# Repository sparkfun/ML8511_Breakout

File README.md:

ML8511 UV Sensor Breakout
=========================

[*ML8511 UV Sensor (SEN-12705)*](https://www.sparkfun.com/products/12705)

The ML8511 sensor detects ultraviolet light in the 280 to 390nm range.

Repository Contents
-------------------

* **/Firmware** - Example firmware for running the sensor
* **/Hardware** - All Eagle design files (.brd, .sch)
* **/Production** - Test bed files and production panel files
 
License Information
-------------------
The hardware is released under [Creative Commons ShareAlike 4.0 International](https://creativecommons.org/licenses/by-sa/4.0/).
The code is beerware; if you see me (or any other SparkFun employee) at the local, and you've found our code helpful, please buy us a round!

Distributed as-is; no warranty is given.

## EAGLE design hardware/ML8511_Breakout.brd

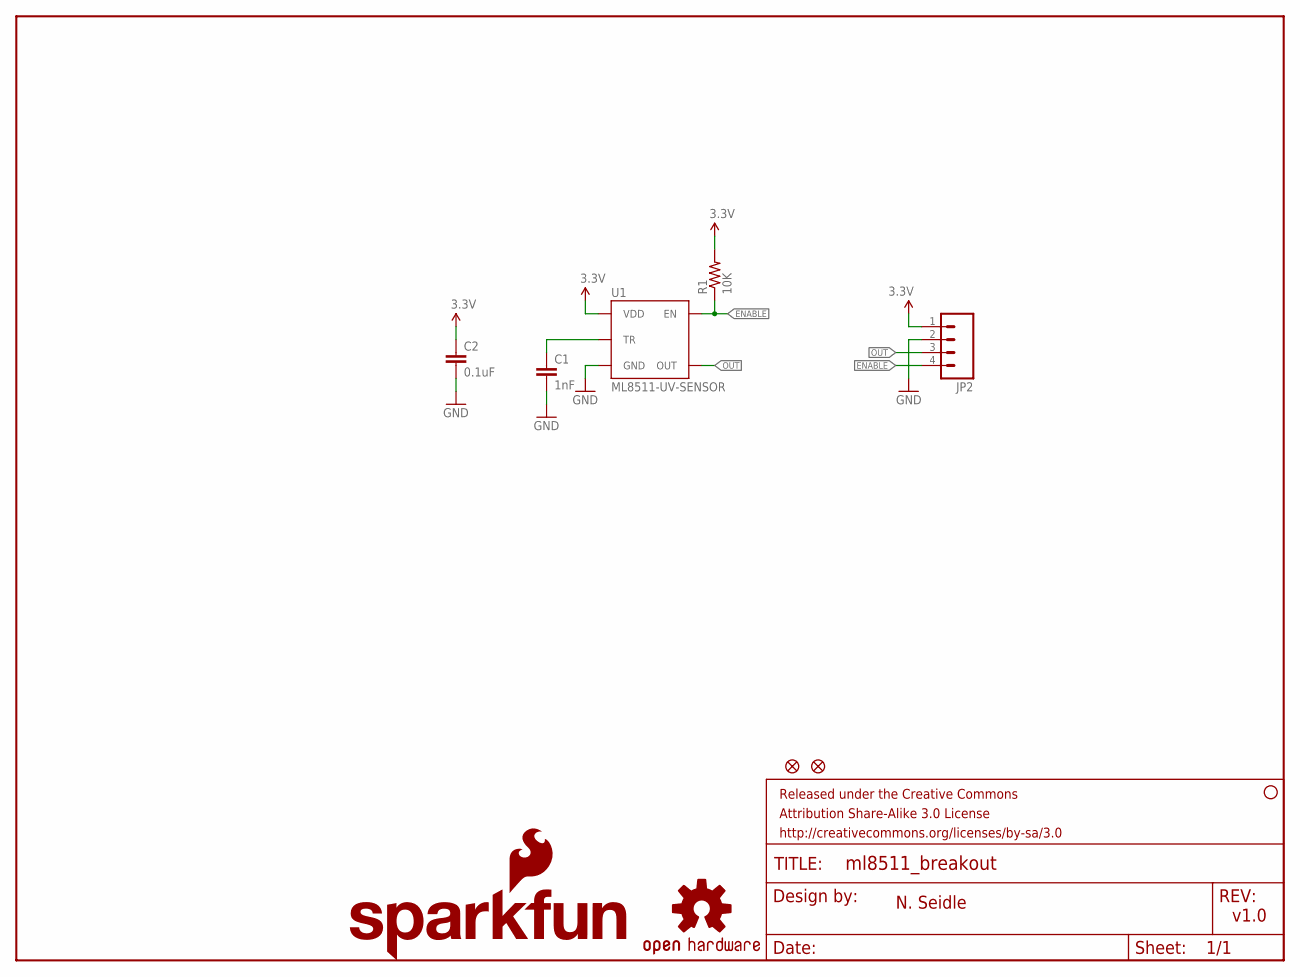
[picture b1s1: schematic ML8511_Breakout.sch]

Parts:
C1: 1nF; 0603-CAP
C2: 0.1uF; 0603-CAP
FID1, FID2: FIDUCIAL1X2; FIDUCIAL-1X2
FRAME2: FRAME-LETTER; CREATIVE_COMMONS
JP2: M04PTH; 1X04
LOGO2: OSHW-LOGOS; OSHW-LOGO-S
LOGO3: SFE_LOGO_FLAME.1_INCH; SFE_LOGO_FLAME_.1
LOGO4: SFE_LOGO_NAME.1_INCH; SFE_LOGO_NAME_.1
R1: 10K; 0603-RES
STANDOFF1: STAND-OFF
U1: ML8511-UV-SENSOR; ML8511

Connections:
3.3V: C2.1, JP2.1, R1.2, U1.7 (VDD)
ENABLE: JP2.4, R1.1, U1.4 (EN)
GND: C1.2, C2.2, JP2.2, U1.5 (GND)
unnamed: C1.1, U1.10 (TR)
OUT: JP2.3, U1.8 (OUT)

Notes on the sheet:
N. Seidle
v1.0

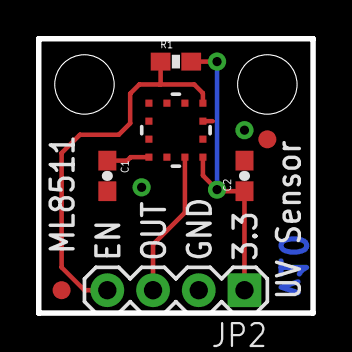
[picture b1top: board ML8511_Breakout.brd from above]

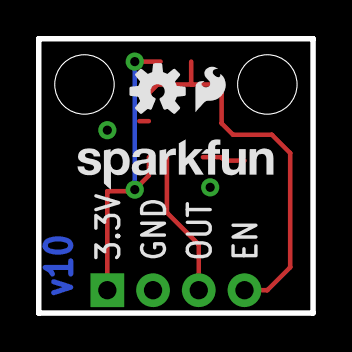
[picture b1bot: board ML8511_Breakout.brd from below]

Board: 2 copper layers, 15.2 x 15.2 mm, 13 parts (3 on the bottom side), 5 nets.

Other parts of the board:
STANDOFF2: STAND-OFF

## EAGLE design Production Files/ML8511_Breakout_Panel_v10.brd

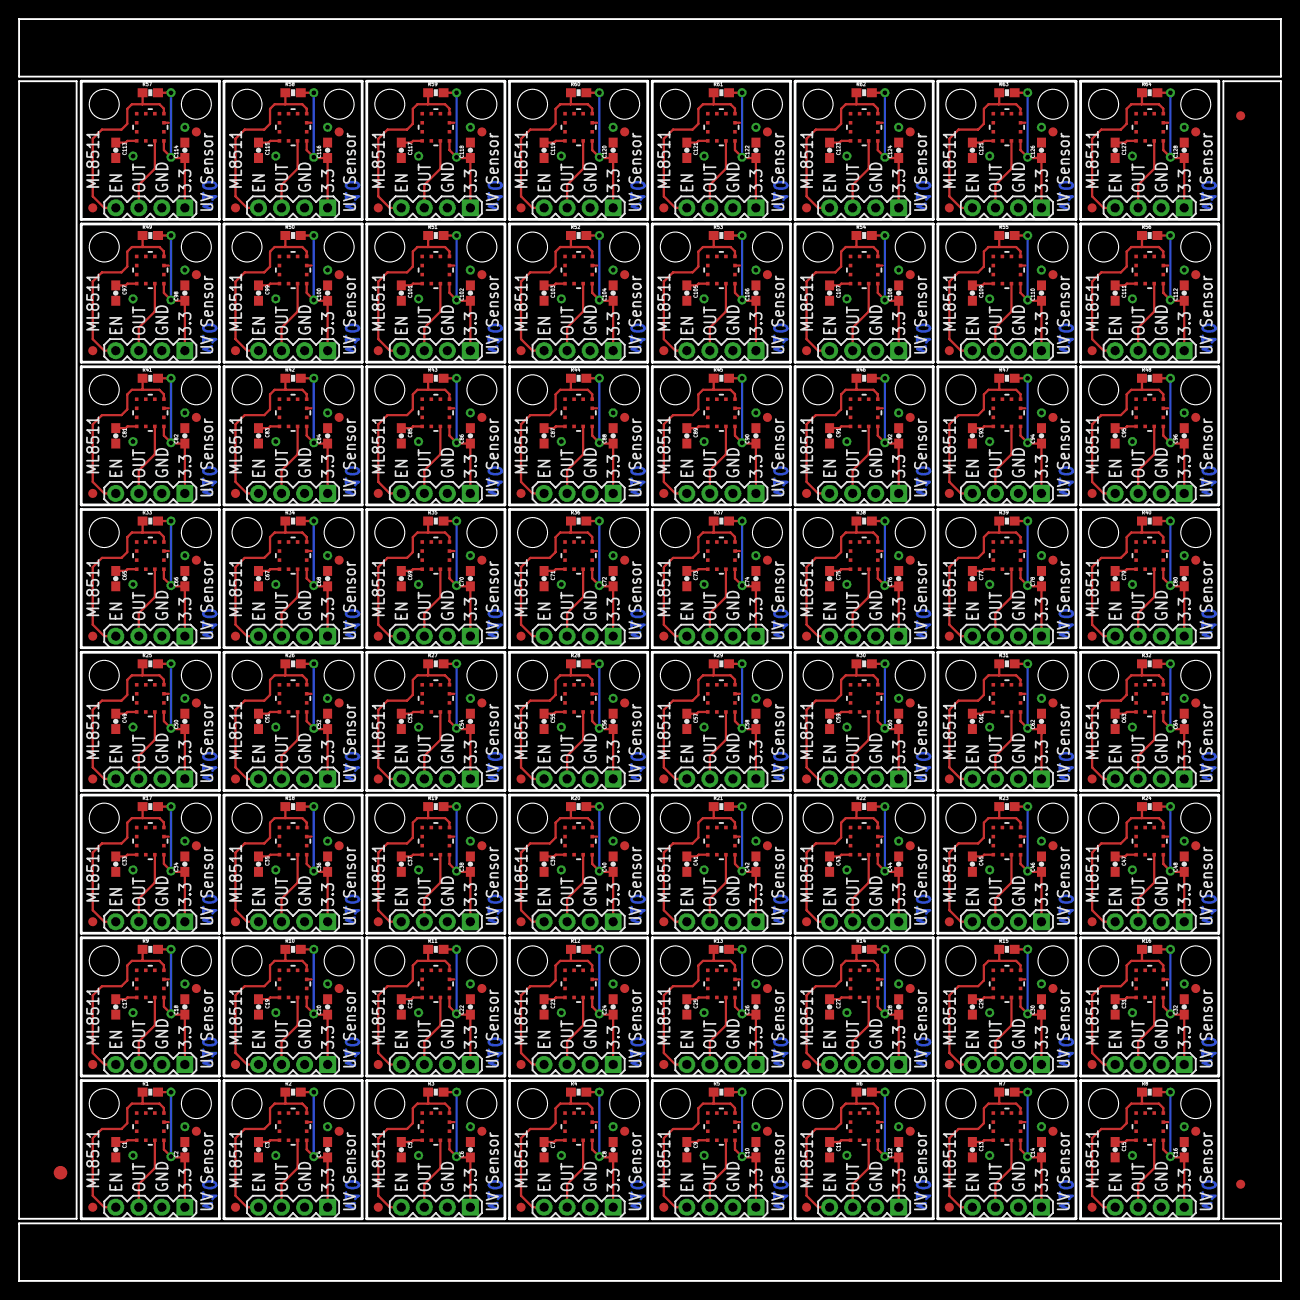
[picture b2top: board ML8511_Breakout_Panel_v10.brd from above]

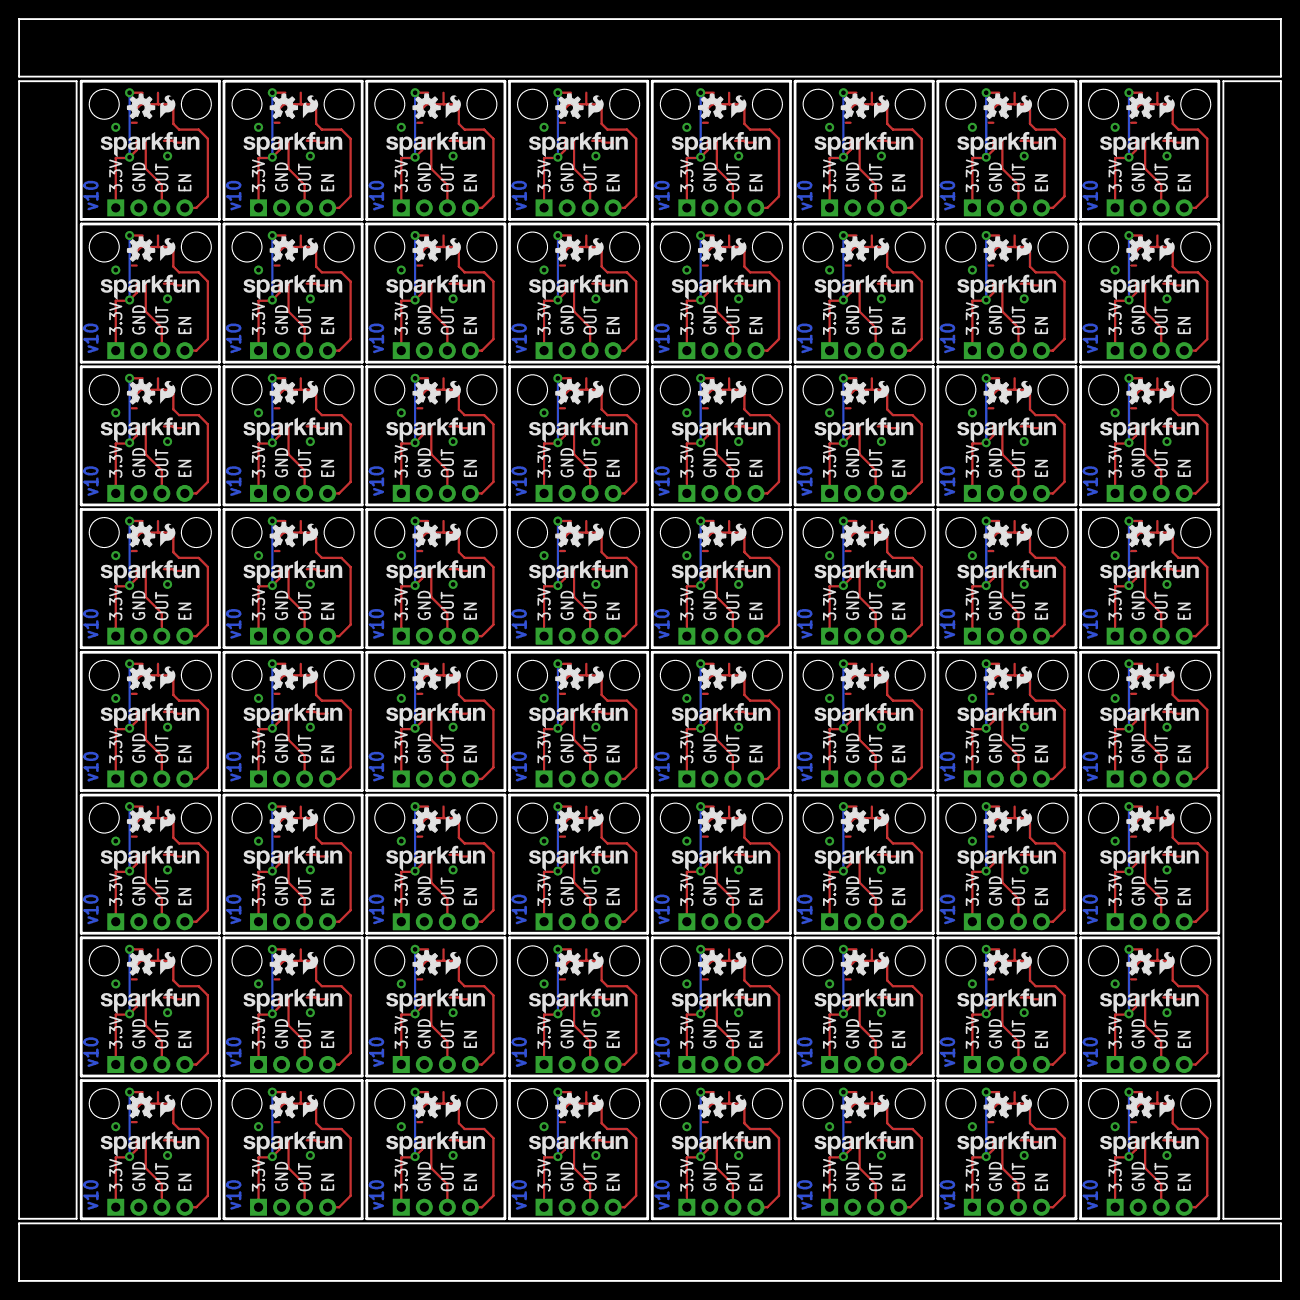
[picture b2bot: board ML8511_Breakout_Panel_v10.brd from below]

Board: 2 copper layers, 139.2 x 139.2 mm, 771 parts (192 on the bottom side), 320 nets.

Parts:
C1, C3, C5, C7, C9, C11, C13, C15, C17, C19, C21, C23, C25, C27, C29, C31, C33, C35, C37, C39, C41, C43, C45, C47, C49, C51, C53, C55, C57, C59, C61, C63, C65, C67, C69, C71, C73, C75, C77, C79, C81, C83, C85, C87, C89, C91, C93, C95, C97, C99, C101, C103, C105, C107, C109, C111, C113, C115, C117, C119, C121, C123, C125, C127: 1nF; 0603-CAP
C2, C4, C6, C8, C10, C12, C14, C16, C18, C20, C22, C24, C26, C28, C30, C32, C34, C36, C38, C40, C42, C44, C46, C48, C50, C52, C54, C56, C58, C60, C62, C64, C66, C68, C70, C72, C74, C76, C78, C80, C82, C84, C86, C88, C90, C92, C94, C96, C98, C100, C102, C104, C106, C108, C110, C112, C114, C116, C118, C120, C122, C124, C126, C128: 0.1uF; 0603-CAP
E$1: FIDUCIAL-1.5X3
E$4, E$5: FIDUCIAL-1X2
FID1, FID2, FID3, FID4, FID5, FID6, FID7, FID8, FID9, FID10, FID11, FID12, FID13, FID14, FID15, FID16, FID17, FID18, FID19, FID20, FID21, FID22, FID23, FID24, FID25, FID26, FID27, FID28, FID29, FID30, FID31, FID32, FID33, FID34, FID35, FID36, FID37, FID38, FID39, FID40, FID41, FID42, FID43, FID44, FID45, FID46, FID47, FID48, FID49, FID50, FID51, FID52, FID53, FID54, FID55, FID56, FID57, FID58, FID59, FID60, FID61, FID62, FID63, FID64, FID65, FID66, FID67, FID68, FID69, FID70, FID71, FID72, FID73, FID74, FID75, FID76, FID77, FID78, FID79, FID80, FID81, FID82, FID83, FID84, FID85, FID86, FID87, FID88, FID89, FID90, FID91, FID92, FID93, FID94, FID95, FID96, FID97, FID98, FID99, FID100, FID101, FID102, FID103, FID104, FID105, FID106, FID107, FID108, FID109, FID110, FID111, FID112, FID113, FID114, FID115, FID116, FID117, FID118, FID119, FID120, FID121, FID122, FID123, FID124, FID125, FID126, FID127, FID128: FIDUCIAL1X2; FIDUCIAL-1X2
JP1, JP2, JP3, JP4, JP5, JP6, JP7, JP8, JP9, JP10, JP11, JP12, JP13, JP14, JP15, JP16, JP17, JP18, JP19, JP20, JP21, JP22, JP23, JP24, JP25, JP26, JP27, JP28, JP29, JP30, JP31, JP32, JP33, JP34, JP35, JP36, JP37, JP38, JP39, JP40, JP41, JP42, JP43, JP44, JP45, JP46, JP47, JP48, JP49, JP50, JP51, JP52, JP53, JP54, JP55, JP56, JP57, JP58, JP59, JP60, JP61, JP62, JP63, JP64: 1X04
LOGO1, LOGO2, LOGO7, LOGO10, LOGO13, LOGO16, LOGO19, LOGO22, LOGO25, LOGO28, LOGO31, LOGO34, LOGO37, LOGO40, LOGO43, LOGO46, LOGO49, LOGO52, LOGO55, LOGO58, LOGO61, LOGO64, LOGO67, LOGO70, LOGO73, LOGO76, LOGO79, LOGO82, LOGO85, LOGO88, LOGO91, LOGO94, LOGO97, LOGO100, LOGO103, LOGO106, LOGO109, LOGO112, LOGO115, LOGO118, LOGO121, LOGO124, LOGO127, LOGO130, LOGO133, LOGO136, LOGO139, LOGO142, LOGO145, LOGO148, LOGO151, LOGO154, LOGO157, LOGO160, LOGO163, LOGO166, LOGO169, LOGO172, LOGO175, LOGO178, LOGO181, LOGO184, LOGO187, LOGO190: OSHW-LOGOS; OSHW-LOGO-S
LOGO3, LOGO5, LOGO8, LOGO11, LOGO14, LOGO17, LOGO20, LOGO23, LOGO26, LOGO29, LOGO32, LOGO35, LOGO38, LOGO41, LOGO44, LOGO47, LOGO50, LOGO53, LOGO56, LOGO59, LOGO62, LOGO65, LOGO68, LOGO71, LOGO74, LOGO77, LOGO80, LOGO83, LOGO86, LOGO89, LOGO92, LOGO95, LOGO98, LOGO101, LOGO104, LOGO107, LOGO110, LOGO113, LOGO116, LOGO119, LOGO122, LOGO125, LOGO128, LOGO131, LOGO134, LOGO137, LOGO140, LOGO143, LOGO146, LOGO149, LOGO152, LOGO155, LOGO158, LOGO161, LOGO164, LOGO167, LOGO170, LOGO173, LOGO176, LOGO179, LOGO182, LOGO185, LOGO188, LOGO191: SFE_LOGO_FLAME.1_INCH; SFE_LOGO_FLAME_.1
LOGO4, LOGO6, LOGO9, LOGO12, LOGO15, LOGO18, LOGO21, LOGO24, LOGO27, LOGO30, LOGO33, LOGO36, LOGO39, LOGO42, LOGO45, LOGO48, LOGO51, LOGO54, LOGO57, LOGO60, LOGO63, LOGO66, LOGO69, LOGO72, LOGO75, LOGO78, LOGO81, LOGO84, LOGO87, LOGO90, LOGO93, LOGO96, LOGO99, LOGO102, LOGO105, LOGO108, LOGO111, LOGO114, LOGO117, LOGO120, LOGO123, LOGO126, LOGO129, LOGO132, LOGO135, LOGO138, LOGO141, LOGO144, LOGO147, LOGO150, LOGO153, LOGO156, LOGO159, LOGO162, LOGO165, LOGO168, LOGO171, LOGO174, LOGO177, LOGO180, LOGO183, LOGO186, LOGO189, LOGO192: SFE_LOGO_NAME.1_INCH; SFE_LOGO_NAME_.1
R1, R2, R3, R4, R5, R6, R7, R8, R9, R10, R11, R12, R13, R14, R15, R16, R17, R18, R19, R20, R21, R22, R23, R24, R25, R26, R27, R28, R29, R30, R31, R32, R33, R34, R35, R36, R37, R38, R39, R40, R41, R42, R43, R44, R45, R46, R47, R48, R49, R50, R51, R52, R53, R54, R55, R56, R57, R58, R59, R60, R61, R62, R63, R64: 10K; 0603-RES
STANDOFF1, STANDOFF2, STANDOFF3, STANDOFF4, STANDOFF5, STANDOFF6, STANDOFF7, STANDOFF8, STANDOFF9, STANDOFF10, STANDOFF11, STANDOFF12, STANDOFF13, STANDOFF14, STANDOFF15, STANDOFF16, STANDOFF17, STANDOFF18, STANDOFF19, STANDOFF20, STANDOFF21, STANDOFF22, STANDOFF23, STANDOFF24, STANDOFF25, STANDOFF26, STANDOFF27, STANDOFF28, STANDOFF29, STANDOFF30, STANDOFF31, STANDOFF32, STANDOFF33, STANDOFF34, STANDOFF35, STANDOFF36, STANDOFF37, STANDOFF38, STANDOFF39, STANDOFF40, STANDOFF41, STANDOFF42, STANDOFF43, STANDOFF44, STANDOFF45, STANDOFF46, STANDOFF47, STANDOFF48, STANDOFF49, STANDOFF50, STANDOFF51, STANDOFF52, STANDOFF53, STANDOFF54, STANDOFF55, STANDOFF56, STANDOFF57, STANDOFF58, STANDOFF59, STANDOFF60, STANDOFF61, STANDOFF62, STANDOFF63, STANDOFF64, STANDOFF65, STANDOFF66, STANDOFF67, STANDOFF68, STANDOFF69, STANDOFF70, STANDOFF71, STANDOFF72, STANDOFF73, STANDOFF74, STANDOFF75, STANDOFF76, STANDOFF77, STANDOFF78, STANDOFF79, STANDOFF80, STANDOFF81, STANDOFF82, STANDOFF83, STANDOFF84, STANDOFF85, STANDOFF86, STANDOFF87, STANDOFF88, STANDOFF89, STANDOFF90, STANDOFF91, STANDOFF92, STANDOFF93, STANDOFF94, STANDOFF95, STANDOFF96, STANDOFF97, STANDOFF98, STANDOFF99, STANDOFF100, STANDOFF101, STANDOFF102, STANDOFF103, STANDOFF104, STANDOFF105, STANDOFF106, STANDOFF107, STANDOFF108, STANDOFF109, STANDOFF110, STANDOFF111, STANDOFF112, STANDOFF113, STANDOFF114, STANDOFF115, STANDOFF116, STANDOFF117, STANDOFF118, STANDOFF119, STANDOFF120, STANDOFF121, STANDOFF122, STANDOFF123, STANDOFF124, STANDOFF125, STANDOFF126, STANDOFF127, STANDOFF128: STAND-OFF
U1, U2, U3, U4, U5, U6, U7, U8, U9, U10, U11, U12, U13, U14, U15, U16, U17, U18, U19, U20, U21, U22, U23, U24, U25, U26, U27, U28, U29, U30, U31, U32, U33, U34, U35, U36, U37, U38, U39, U40, U41, U42, U43, U44, U45, U46, U47, U48, U49, U50, U51, U52, U53, U54, U55, U56, U57, U58, U59, U60, U61, U62, U63, U64: ML8511-UV-SENSOR; ML8511

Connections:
3.3V: C2.1, JP2.1, R1.2, U1.7
3.3V1: C4.1, JP1.1, R2.2, U2.7
3.3V2: C6.1, JP3.1, R3.2, U3.7
3.3V3: C8.1, JP4.1, R4.2, U4.7
3.3V4: C10.1, JP5.1, R5.2, U5.7
3.3V5: C12.1, JP6.1, R6.2, U6.7
3.3V6: C14.1, JP7.1, R7.2, U7.7
3.3V7: C16.1, JP8.1, R8.2, U8.7
3.3V8: C18.1, JP9.1, R9.2, U9.7
3.3V9: C20.1, JP10.1, R10.2, U10.7
3.3V10: C22.1, JP11.1, R11.2, U11.7
3.3V11: C24.1, JP12.1, R12.2, U12.7
3.3V12: C26.1, JP13.1, R13.2, U13.7
3.3V13: C28.1, JP14.1, R14.2, U14.7
3.3V14: C30.1, JP15.1, R15.2, U15.7
3.3V15: C32.1, JP16.1, R16.2, U16.7
3.3V16: C34.1, JP17.1, R17.2, U17.7
3.3V17: C36.1, JP18.1, R18.2, U18.7
3.3V18: C38.1, JP19.1, R19.2, U19.7
3.3V19: C40.1, JP20.1, R20.2, U20.7
3.3V20: C42.1, JP21.1, R21.2, U21.7
3.3V21: C44.1, JP22.1, R22.2, U22.7
3.3V22: C46.1, JP23.1, R23.2, U23.7
3.3V23: C48.1, JP24.1, R24.2, U24.7
3.3V24: C50.1, JP25.1, R25.2, U25.7
3.3V25: C52.1, JP26.1, R26.2, U26.7
3.3V26: C54.1, JP27.1, R27.2, U27.7
3.3V27: C56.1, JP28.1, R28.2, U28.7
3.3V28: C58.1, JP29.1, R29.2, U29.7
3.3V29: C60.1, JP30.1, R30.2, U30.7
3.3V30: C62.1, JP31.1, R31.2, U31.7
3.3V31: C64.1, JP32.1, R32.2, U32.7
3.3V32: C66.1, JP33.1, R33.2, U33.7
3.3V33: C68.1, JP34.1, R34.2, U34.7
3.3V34: C70.1, JP35.1, R35.2, U35.7
3.3V35: C72.1, JP36.1, R36.2, U36.7
3.3V36: C74.1, JP37.1, R37.2, U37.7
3.3V37: C76.1, JP38.1, R38.2, U38.7
3.3V38: C78.1, JP39.1, R39.2, U39.7
3.3V39: C80.1, JP40.1, R40.2, U40.7
3.3V40: C82.1, JP41.1, R41.2, U41.7
3.3V41: C84.1, JP42.1, R42.2, U42.7
3.3V42: C86.1, JP43.1, R43.2, U43.7
3.3V43: C88.1, JP44.1, R44.2, U44.7
3.3V44: C90.1, JP45.1, R45.2, U45.7
3.3V45: C92.1, JP46.1, R46.2, U46.7
3.3V46: C94.1, JP47.1, R47.2, U47.7
3.3V47: C96.1, JP48.1, R48.2, U48.7
3.3V48: C98.1, JP49.1, R49.2, U49.7
3.3V49: C100.1, JP50.1, R50.2, U50.7
3.3V50: C102.1, JP51.1, R51.2, U51.7
3.3V51: C104.1, JP52.1, R52.2, U52.7
3.3V52: C106.1, JP53.1, R53.2, U53.7
3.3V53: C108.1, JP54.1, R54.2, U54.7
3.3V54: C110.1, JP55.1, R55.2, U55.7
3.3V55: C112.1, JP56.1, R56.2, U56.7
3.3V56: C114.1, JP57.1, R57.2, U57.7
3.3V57: C116.1, JP58.1, R58.2, U58.7
3.3V58: C118.1, JP59.1, R59.2, U59.7
3.3V59: C120.1, JP60.1, R60.2, U60.7
3.3V60: C122.1, JP61.1, R61.2, U61.7
3.3V61: C124.1, JP62.1, R62.2, U62.7
3.3V62: C126.1, JP63.1, R63.2, U63.7
3.3V63: C128.1, JP64.1, R64.2, U64.7
ENABLE: JP2.4, R1.1, U1.4
ENABLE1: JP1.4, R2.1, U2.4
ENABLE2: JP3.4, R3.1, U3.4
ENABLE3: JP4.4, R4.1, U4.4
ENABLE4: JP5.4, R5.1, U5.4
ENABLE5: JP6.4, R6.1, U6.4
ENABLE6: JP7.4, R7.1, U7.4
ENABLE7: JP8.4, R8.1, U8.4
ENABLE8: JP9.4, R9.1, U9.4
ENABLE9: JP10.4, R10.1, U10.4
ENABLE10: JP11.4, R11.1, U11.4
ENABLE11: JP12.4, R12.1, U12.4
ENABLE12: JP13.4, R13.1, U13.4
ENABLE13: JP14.4, R14.1, U14.4
ENABLE14: JP15.4, R15.1, U15.4
ENABLE15: JP16.4, R16.1, U16.4
ENABLE16: JP17.4, R17.1, U17.4
ENABLE17: JP18.4, R18.1, U18.4
ENABLE18: JP19.4, R19.1, U19.4
ENABLE19: JP20.4, R20.1, U20.4
ENABLE20: JP21.4, R21.1, U21.4
ENABLE21: JP22.4, R22.1, U22.4
ENABLE22: JP23.4, R23.1, U23.4
ENABLE23: JP24.4, R24.1, U24.4
ENABLE24: JP25.4, R25.1, U25.4
ENABLE25: JP26.4, R26.1, U26.4
ENABLE26: JP27.4, R27.1, U27.4
ENABLE27: JP28.4, R28.1, U28.4
ENABLE28: JP29.4, R29.1, U29.4
ENABLE29: JP30.4, R30.1, U30.4
ENABLE30: JP31.4, R31.1, U31.4
ENABLE31: JP32.4, R32.1, U32.4
ENABLE32: JP33.4, R33.1, U33.4
ENABLE33: JP34.4, R34.1, U34.4
ENABLE34: JP35.4, R35.1, U35.4
ENABLE35: JP36.4, R36.1, U36.4
ENABLE36: JP37.4, R37.1, U37.4
ENABLE37: JP38.4, R38.1, U38.4
ENABLE38: JP39.4, R39.1, U39.4
ENABLE39: JP40.4, R40.1, U40.4
ENABLE40: JP41.4, R41.1, U41.4
ENABLE41: JP42.4, R42.1, U42.4
ENABLE42: JP43.4, R43.1, U43.4
ENABLE43: JP44.4, R44.1, U44.4
ENABLE44: JP45.4, R45.1, U45.4
ENABLE45: JP46.4, R46.1, U46.4
ENABLE46: JP47.4, R47.1, U47.4
ENABLE47: JP48.4, R48.1, U48.4
ENABLE48: JP49.4, R49.1, U49.4
ENABLE49: JP50.4, R50.1, U50.4
ENABLE50: JP51.4, R51.1, U51.4
ENABLE51: JP52.4, R52.1, U52.4
ENABLE52: JP53.4, R53.1, U53.4
ENABLE53: JP54.4, R54.1, U54.4
ENABLE54: JP55.4, R55.1, U55.4
ENABLE55: JP56.4, R56.1, U56.4
ENABLE56: JP57.4, R57.1, U57.4
ENABLE57: JP58.4, R58.1, U58.4
ENABLE58: JP59.4, R59.1, U59.4
ENABLE59: JP60.4, R60.1, U60.4
ENABLE60: JP61.4, R61.1, U61.4
ENABLE61: JP62.4, R62.1, U62.4
ENABLE62: JP63.4, R63.1, U63.4
ENABLE63: JP64.4, R64.1, U64.4
GND: C1.2, C2.2, JP2.2, U1.5
GND1: C3.2, C4.2, JP1.2, U2.5
GND2: C5.2, C6.2, JP3.2, U3.5
GND3: C7.2, C8.2, JP4.2, U4.5
GND4: C9.2, C10.2, JP5.2, U5.5
GND5: C11.2, C12.2, JP6.2, U6.5
GND6: C13.2, C14.2, JP7.2, U7.5
GND7: C15.2, C16.2, JP8.2, U8.5
GND8: C17.2, C18.2, JP9.2, U9.5
GND9: C19.2, C20.2, JP10.2, U10.5
GND10: C21.2, C22.2, JP11.2, U11.5
GND11: C23.2, C24.2, JP12.2, U12.5
GND12: C25.2, C26.2, JP13.2, U13.5
GND13: C27.2, C28.2, JP14.2, U14.5
GND14: C29.2, C30.2, JP15.2, U15.5
GND15: C31.2, C32.2, JP16.2, U16.5
GND16: C33.2, C34.2, JP17.2, U17.5
GND17: C35.2, C36.2, JP18.2, U18.5
GND18: C37.2, C38.2, JP19.2, U19.5
GND19: C39.2, C40.2, JP20.2, U20.5
GND20: C41.2, C42.2, JP21.2, U21.5
GND21: C43.2, C44.2, JP22.2, U22.5
GND22: C45.2, C46.2, JP23.2, U23.5
GND23: C47.2, C48.2, JP24.2, U24.5
GND24: C49.2, C50.2, JP25.2, U25.5
GND25: C51.2, C52.2, JP26.2, U26.5
GND26: C53.2, C54.2, JP27.2, U27.5
GND27: C55.2, C56.2, JP28.2, U28.5
GND28: C57.2, C58.2, JP29.2, U29.5
GND29: C59.2, C60.2, JP30.2, U30.5
GND30: C61.2, C62.2, JP31.2, U31.5
GND31: C63.2, C64.2, JP32.2, U32.5
GND32: C65.2, C66.2, JP33.2, U33.5
GND33: C67.2, C68.2, JP34.2, U34.5
GND34: C69.2, C70.2, JP35.2, U35.5
GND35: C71.2, C72.2, JP36.2, U36.5
GND36: C73.2, C74.2, JP37.2, U37.5
GND37: C75.2, C76.2, JP38.2, U38.5
GND38: C77.2, C78.2, JP39.2, U39.5
GND39: C79.2, C80.2, JP40.2, U40.5
GND40: C81.2, C82.2, JP41.2, U41.5
GND41: C83.2, C84.2, JP42.2, U42.5
GND42: C85.2, C86.2, JP43.2, U43.5
GND43: C87.2, C88.2, JP44.2, U44.5
GND44: C89.2, C90.2, JP45.2, U45.5
GND45: C91.2, C92.2, JP46.2, U46.5
GND46: C93.2, C94.2, JP47.2, U47.5
GND47: C95.2, C96.2, JP48.2, U48.5
GND48: C97.2, C98.2, JP49.2, U49.5
GND49: C99.2, C100.2, JP50.2, U50.5
GND50: C101.2, C102.2, JP51.2, U51.5
GND51: C103.2, C104.2, JP52.2, U52.5
GND52: C105.2, C106.2, JP53.2, U53.5
GND53: C107.2, C108.2, JP54.2, U54.5
GND54: C109.2, C110.2, JP55.2, U55.5
GND55: C111.2, C112.2, JP56.2, U56.5
GND56: C113.2, C114.2, JP57.2, U57.5
GND57: C115.2, C116.2, JP58.2, U58.5
GND58: C117.2, C118.2, JP59.2, U59.5
GND59: C119.2, C120.2, JP60.2, U60.5
GND60: C121.2, C122.2, JP61.2, U61.5
GND61: C123.2, C124.2, JP62.2, U62.5
GND62: C125.2, C126.2, JP63.2, U63.5
GND63: C127.2, C128.2, JP64.2, U64.5
unnamed: C3.1, U2.10
unnamed: C5.1, U3.10
unnamed: C1.1, U1.10
unnamed: C7.1, U4.10
unnamed: C9.1, U5.10
unnamed: C11.1, U6.10
unnamed: C13.1, U7.10
unnamed: C15.1, U8.10
unnamed: C17.1, U9.10
unnamed: C19.1, U10.10
unnamed: C21.1, U11.10
unnamed: C23.1, U12.10
unnamed: C25.1, U13.10
unnamed: C27.1, U14.10
unnamed: C29.1, U15.10
unnamed: C31.1, U16.10
unnamed: C33.1, U17.10
unnamed: C35.1, U18.10
unnamed: C37.1, U19.10
unnamed: C39.1, U20.10
unnamed: C41.1, U21.10
unnamed: C43.1, U22.10
unnamed: C45.1, U23.10
unnamed: C47.1, U24.10
unnamed: C49.1, U25.10
unnamed: C51.1, U26.10
unnamed: C53.1, U27.10
unnamed: C55.1, U28.10
unnamed: C57.1, U29.10
unnamed: C59.1, U30.10
unnamed: C61.1, U31.10
unnamed: C63.1, U32.10
unnamed: C65.1, U33.10
unnamed: C67.1, U34.10
unnamed: C69.1, U35.10
unnamed: C71.1, U36.10
unnamed: C73.1, U37.10
unnamed: C75.1, U38.10
unnamed: C77.1, U39.10
unnamed: C79.1, U40.10
unnamed: C81.1, U41.10
unnamed: C83.1, U42.10
unnamed: C85.1, U43.10
unnamed: C87.1, U44.10
unnamed: C89.1, U45.10
unnamed: C91.1, U46.10
unnamed: C93.1, U47.10
unnamed: C95.1, U48.10
unnamed: C97.1, U49.10
unnamed: C99.1, U50.10
unnamed: C101.1, U51.10
unnamed: C103.1, U52.10
unnamed: C105.1, U53.10
unnamed: C107.1, U54.10
unnamed: C109.1, U55.10
unnamed: C111.1, U56.10
unnamed: C113.1, U57.10
unnamed: C115.1, U58.10
unnamed: C117.1, U59.10
unnamed: C119.1, U60.10
unnamed: C121.1, U61.10
unnamed: C123.1, U62.10
unnamed: C125.1, U63.10
unnamed: C127.1, U64.10
OUT: JP2.3, U1.8
OUT1: JP1.3, U2.8
OUT2: JP3.3, U3.8
OUT3: JP4.3, U4.8
OUT4: JP5.3, U5.8
OUT5: JP6.3, U6.8
OUT6: JP7.3, U7.8
OUT7: JP8.3, U8.8
OUT8: JP9.3, U9.8
OUT9: JP10.3, U10.8
OUT10: JP11.3, U11.8
OUT11: JP12.3, U12.8
OUT12: JP13.3, U13.8
OUT13: JP14.3, U14.8
OUT14: JP15.3, U15.8
OUT15: JP16.3, U16.8
OUT16: JP17.3, U17.8
OUT17: JP18.3, U18.8
OUT18: JP19.3, U19.8
OUT19: JP20.3, U20.8
OUT20: JP21.3, U21.8
OUT21: JP22.3, U22.8
OUT22: JP23.3, U23.8
OUT23: JP24.3, U24.8
OUT24: JP25.3, U25.8
OUT25: JP26.3, U26.8
OUT26: JP27.3, U27.8
OUT27: JP28.3, U28.8
OUT28: JP29.3, U29.8
OUT29: JP30.3, U30.8
OUT30: JP31.3, U31.8
OUT31: JP32.3, U32.8
OUT32: JP33.3, U33.8
OUT33: JP34.3, U34.8
OUT34: JP35.3, U35.8
OUT35: JP36.3, U36.8
OUT36: JP37.3, U37.8
OUT37: JP38.3, U38.8
OUT38: JP39.3, U39.8
OUT39: JP40.3, U40.8
OUT40: JP41.3, U41.8
OUT41: JP42.3, U42.8
OUT42: JP43.3, U43.8
OUT43: JP44.3, U44.8
OUT44: JP45.3, U45.8
OUT45: JP46.3, U46.8
OUT46: JP47.3, U47.8
OUT47: JP48.3, U48.8
OUT48: JP49.3, U49.8
OUT49: JP50.3, U50.8
OUT50: JP51.3, U51.8
OUT51: JP52.3, U52.8
OUT52: JP53.3, U53.8
OUT53: JP54.3, U54.8
OUT54: JP55.3, U55.8
OUT55: JP56.3, U56.8
OUT56: JP57.3, U57.8
OUT57: JP58.3, U58.8
OUT58: JP59.3, U59.8
OUT59: JP60.3, U60.8
OUT60: JP61.3, U61.8
OUT61: JP62.3, U62.8
OUT62: JP63.3, U63.8
OUT63: JP64.3, U64.8

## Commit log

2014-01-02 Small changes to layout.
2014-01-16 Added example sketch. Just an ADC with some ratios and mapping.
    Sensor outputs 1V to 3V. Uses the 3.3V as a reference and maps to
    mW/cm^2.
2014-01-16 DFM Changes
    1.) Modified 3.3V trace so junction is not on IC pad
    2.) Added trestrict under IC
    3.) Routed GND trace directly away from IC
    4.) Modified silk to better incorporate OSHW logo
    5.) Version numbers between sch and brd are now consistent at v10
2014-01-16 Minor silk fix
    EN bsilk needed a scoot.
2014-01-16 Fixed silk error. Updated readme.
    Fixed silk from MP8511 to ML8511.
2014-01-23 added local fiducials
2014-01-23 created panel
2014-03-13 Updating README and repo for public release
2014-03-23 Fixed readme. Added fritzing part.
2014-03-23 Readme update.

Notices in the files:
parts and their libraries:
SparkFun-Connectors: Licensing: CC v3.0 Share-Alike You are welcome to use this library for commercial purposes.
SparkFun-Aesthetics: Released under the Creative Commons Attribution Share-Alike 3.0 License
SparkFun-Aesthetics: http://creativecommons.org/licenses/by-sa/3.0
